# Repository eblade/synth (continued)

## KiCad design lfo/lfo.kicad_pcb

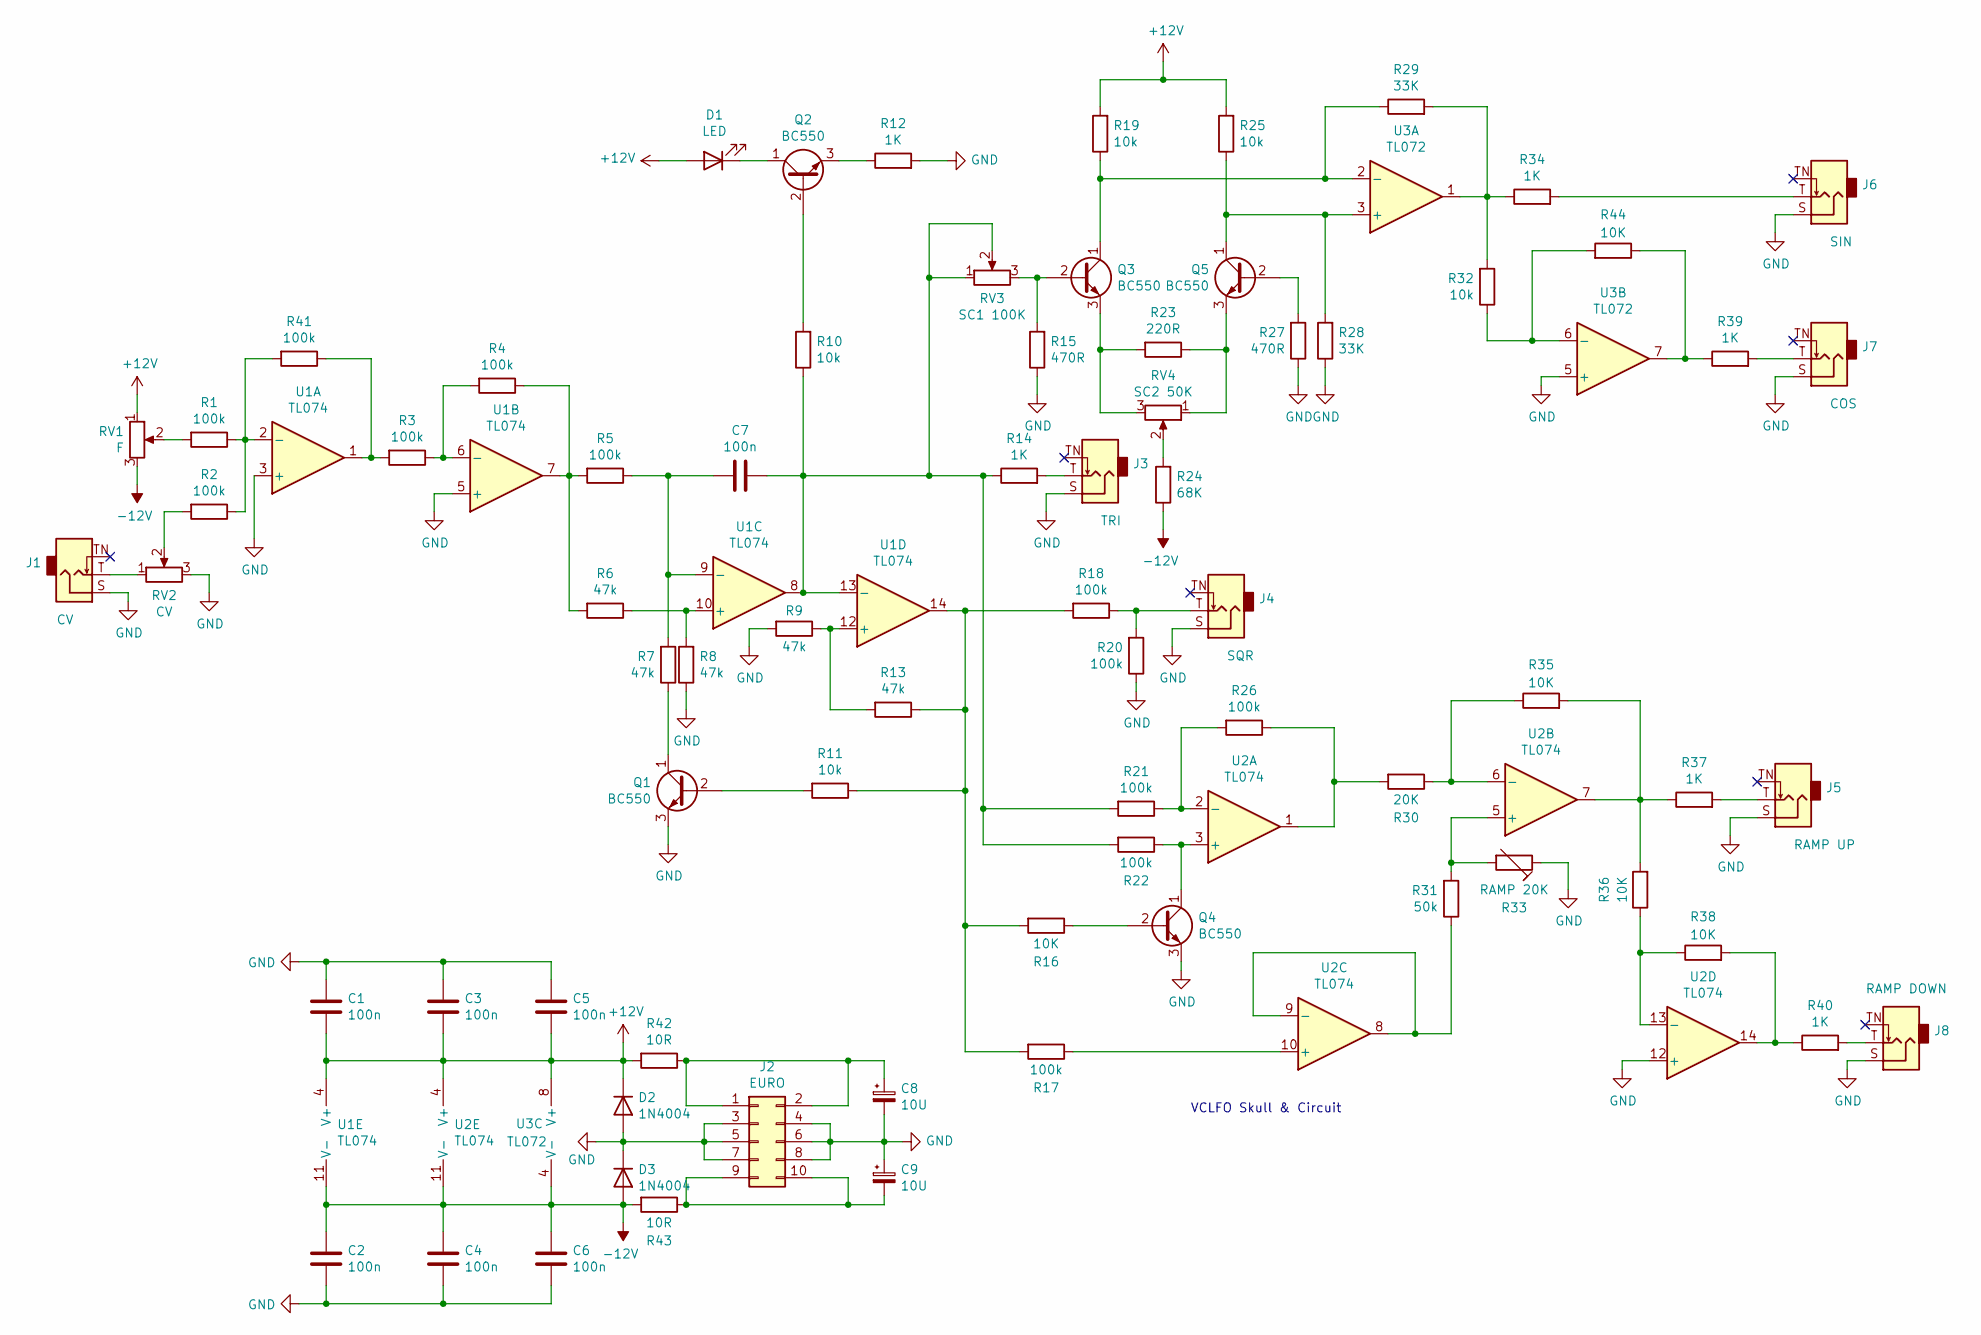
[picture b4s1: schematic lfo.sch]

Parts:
C1, C2, C3, C4, C5, C6, C7: 100n; C_Disc_D5.0mm_W2.5mm_P2.50mm
C8, C9: 10U; CP_Radial_D5.0mm_P2.00mm
D1: LED; LED_D3.0mm
D2, D3: 1N4004; D_5W_P12.70mm_Horizontal
J1: CV; Jack_3.5mm_QingPu_WQP-PJ398SM_Vertical_CircularHoles
J2: EURO; PinHeader_2x05_P2.54mm_Vertical
J3: TRI; Jack_3.5mm_QingPu_WQP-PJ398SM_Vertical_CircularHoles
J4: SQR; Jack_3.5mm_QingPu_WQP-PJ398SM_Vertical_CircularHoles
J5: RAMP UP; Jack_3.5mm_QingPu_WQP-PJ398SM_Vertical_CircularHoles
J6: SIN; Jack_3.5mm_QingPu_WQP-PJ398SM_Vertical_CircularHoles
J7: COS; Jack_3.5mm_QingPu_WQP-PJ398SM_Vertical_CircularHoles
J8: RAMP DOWN; Jack_3.5mm_QingPu_WQP-PJ398SM_Vertical_CircularHoles
Q1, Q2, Q3, Q4, Q5: BC550; TO-92_Inline
R1, R2, R3, R4, R5, R17, R18, R20, R21, R22, R26, R41: 100k; R_Axial_DIN0204_L3.6mm_D1.6mm_P7.62mm_Horizontal
R6, R7, R8, R9, R13: 47k; R_Axial_DIN0204_L3.6mm_D1.6mm_P7.62mm_Horizontal
R10, R11, R19, R25, R32: 10k; R_Axial_DIN0204_L3.6mm_D1.6mm_P7.62mm_Horizontal
R12, R14, R34, R37, R39, R40: 1K; R_Axial_DIN0204_L3.6mm_D1.6mm_P7.62mm_Horizontal
R15, R27: 470R; R_Axial_DIN0204_L3.6mm_D1.6mm_P7.62mm_Horizontal
R16, R35, R36, R38, R44: 10K; R_Axial_DIN0204_L3.6mm_D1.6mm_P7.62mm_Horizontal
R23: 220R; R_Axial_DIN0204_L3.6mm_D1.6mm_P7.62mm_Horizontal
R24: 68K; R_Axial_DIN0204_L3.6mm_D1.6mm_P7.62mm_Horizontal
R28, R29: 33K; R_Axial_DIN0204_L3.6mm_D1.6mm_P7.62mm_Horizontal
R30: 20K; R_Axial_DIN0204_L3.6mm_D1.6mm_P7.62mm_Horizontal
R31: 50k; R_Axial_DIN0204_L3.6mm_D1.6mm_P7.62mm_Horizontal
R33: RAMP 20K; Potentiometer_Bourns_3296W_Vertical
R42, R43: 10R; R_Axial_DIN0204_L3.6mm_D1.6mm_P7.62mm_Horizontal
RV1: F; Potentiometer_Alps_RK09L_Single_Vertical
RV2: CV; Potentiometer_Alps_RK09L_Single_Vertical
RV3: SC1 100K; Potentiometer_Bourns_3296W_Vertical
RV4: SC2 50K; Potentiometer_Bourns_3296W_Vertical
U1, U2: TL074; DIP-14_W7.62mm_Socket_LongPads
U3: TL072; DIP-8_W7.62mm_Socket_LongPads

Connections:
+12V: C1.1, C3.1, C5.1, D1.2 (A), D2.1 (K), R19.2, R25.2, R42.2, RV1.1, U1.4 (V+), U2.4 (V+), U3.8 (V+)
-12V: C2.2, C4.2, C6.2, D3.2 (A), R24.1, R43.2, RV1.3, U1.11 (V-), U2.11 (V-), U3.4 (V-)
GND: C1.2, C2.1, C3.2, C4.1, C5.2, C6.1, C8.2, C9.1, D2.2 (A), D3.1 (K), J1.S, J2.3, J2.4, J2.5, J2.6, J2.7, J2.8, J3.S, J4.S, J5.S, J6.S, J7.S, J8.S, Q1.3 (E), Q4.3 (E), R8.1, R9.2, R12.2, R15.1, R20.1, R27.1, R28.1, R33.1, RV2.3, U1.3 (+), U1.5 (+), U2.12 (+), U3.5 (+)
unnamed: C7.1, R10.1, R14.1, R21.2, R22.2, RV3.1, RV3.2, U1.8, U1.13 (-)
unnamed: C7.2, R5.1, R7.2, U1.9 (-)
unnamed: C8.1, J2.1, J2.2, R42.1
unnamed: C9.2, J2.9, J2.10, R43.1
unnamed: D1.1 (K), Q2.1 (C)
unnamed: J1.T, RV2.1
unnamed: J3.T, R14.2
unnamed: J4.T, R18.1, R20.2
unnamed: J5.T, R37.2
unnamed: J6.T, R34.2
unnamed: J7.T, R39.2
unnamed: J8.T, R40.2
unnamed: Q1.1 (C), R7.1
unnamed: Q1.2 (B), R11.2
unnamed: Q2.2 (B), R10.2
unnamed: Q2.3 (E), R12.1
unnamed: Q3.1 (C), R19.1, R29.1, U3.2 (-)
unnamed: Q3.2 (B), R15.2, RV3.3
unnamed: Q3.3 (E), R23.2, RV4.3
unnamed: Q4.1 (C), R22.1, U2.3 (+)
unnamed: Q4.2 (B), R16.1
unnamed: Q5.1 (C), R25.1, R28.2, U3.3 (+)
unnamed: Q5.2 (B), R27.2
unnamed: Q5.3 (E), R23.1, RV4.1
unnamed: R1.1, R2.1, R41.2, U1.2 (-)
unnamed: R1.2, RV1.2
unnamed: R2.2, RV2.2
unnamed: R3.1, R4.2, U1.6 (-)
unnamed: R3.2, R41.1, U1.1
unnamed: R4.1, R5.2, R6.2, U1.7
unnamed: R6.1, R8.2, U1.10 (+)
unnamed: R11.1, R13.1, R16.2, R17.2, R18.2, U1.14
unnamed: R9.1, R13.2, U1.12 (+)
unnamed: R17.1, U2.10 (+)
unnamed: R21.1, R26.2, U2.2 (-)
unnamed: R24.2, RV4.2
unnamed: R26.1, R30.2, U2.1
unnamed: R29.2, R32.2, R34.1, U3.1
unnamed: R30.1, R35.1, U2.6 (-)
unnamed: R31.1, U2.8, U2.9 (-)
unnamed: R31.2, R33.2, U2.5 (+)
unnamed: R32.1, R44.2, U3.6 (-)
unnamed: R35.2, R36.2, R37.1, U2.7
unnamed: R36.1, R38.1, U2.13 (-)
unnamed: R38.2, R40.1, U2.14
unnamed: R39.1, R44.1, U3.7

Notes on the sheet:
VCLFO Skull & Circuit

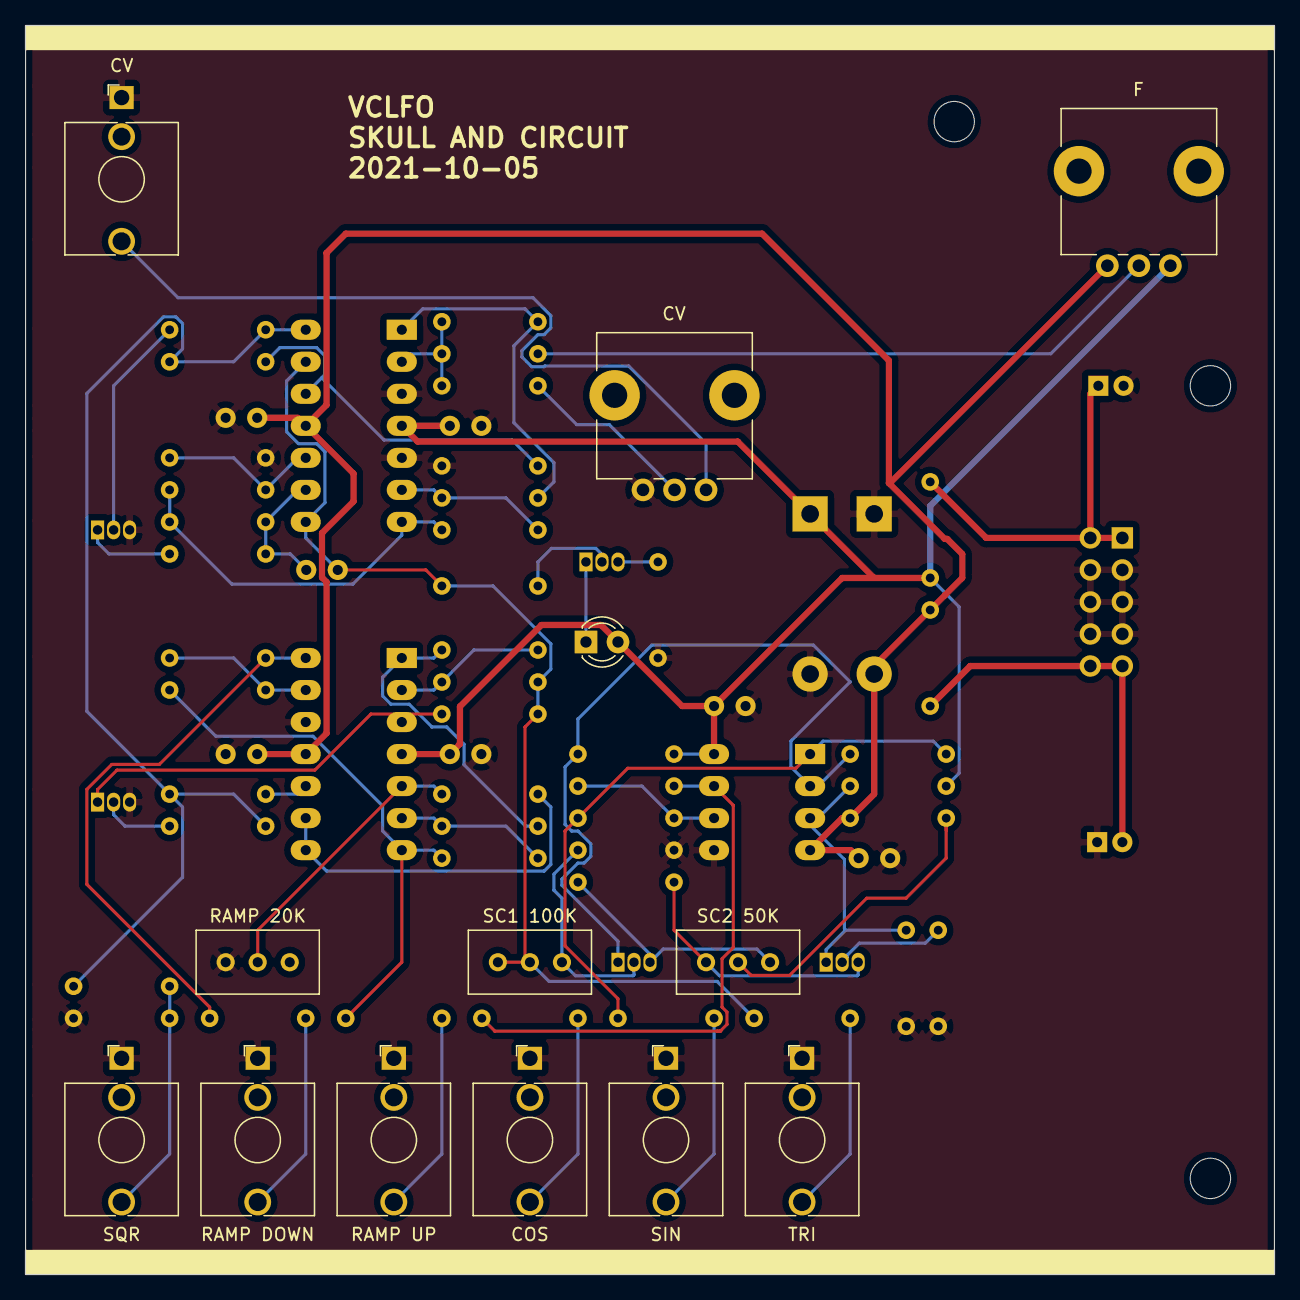
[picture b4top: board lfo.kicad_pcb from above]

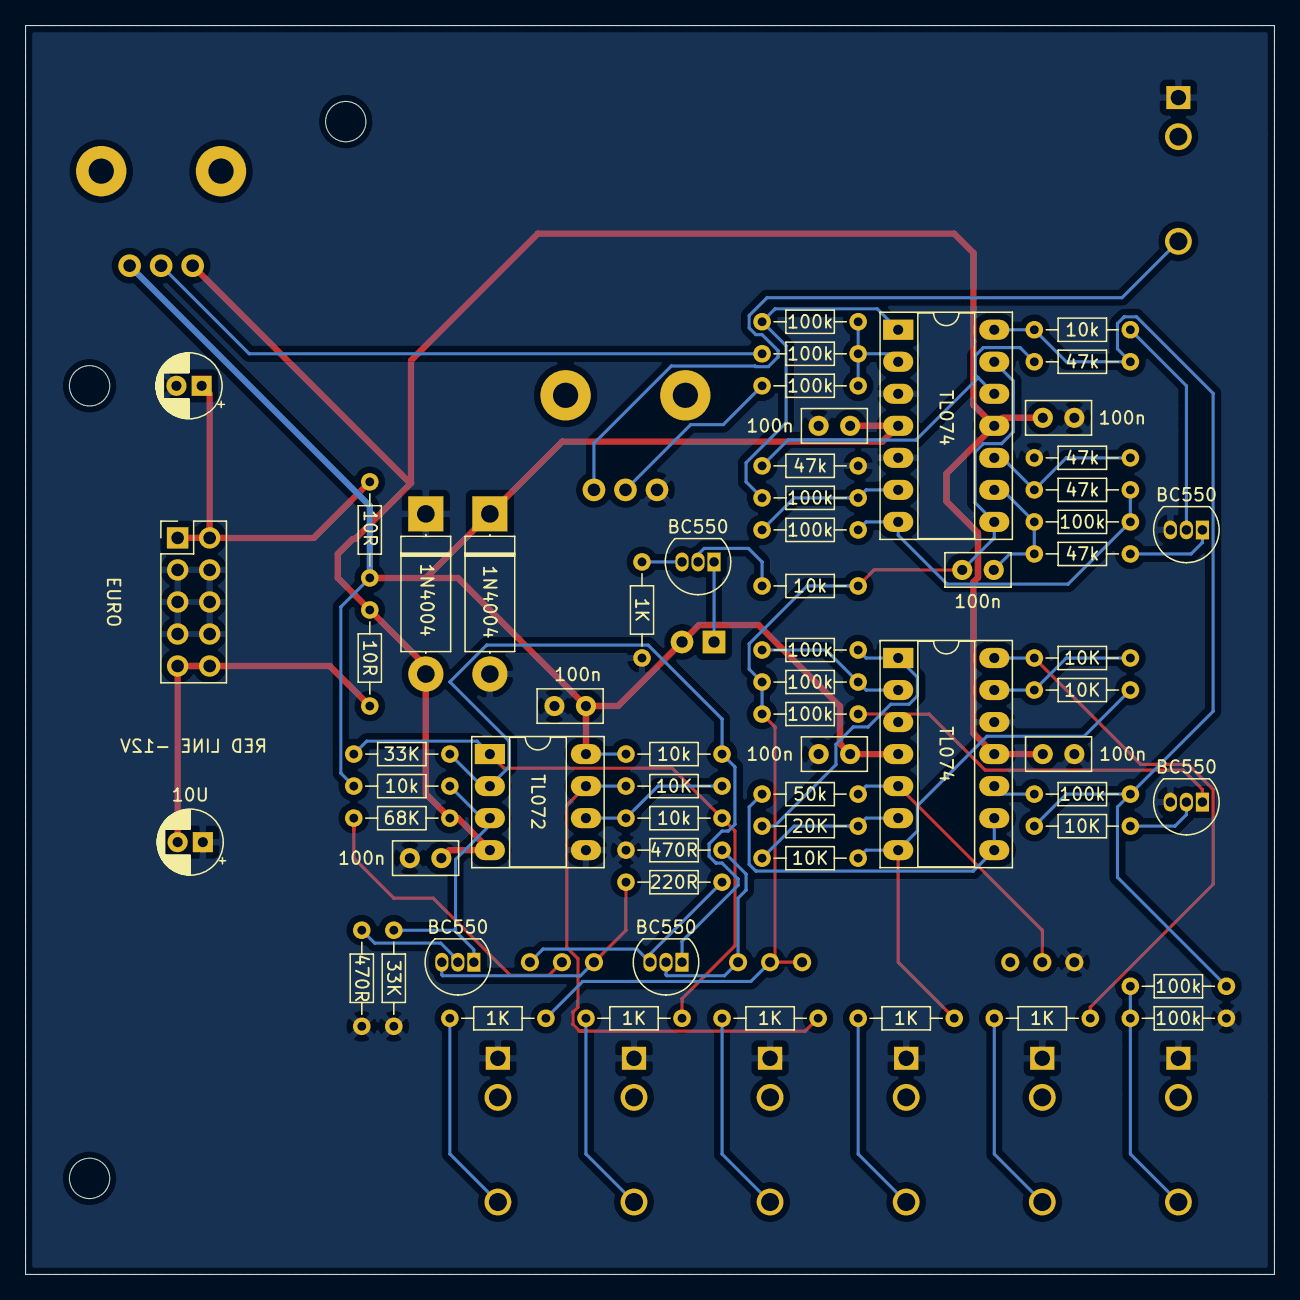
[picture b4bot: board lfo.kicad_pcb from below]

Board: 2 copper layers, 99.1 x 99.1 mm, 76 parts (63 on the bottom side), 49 nets.

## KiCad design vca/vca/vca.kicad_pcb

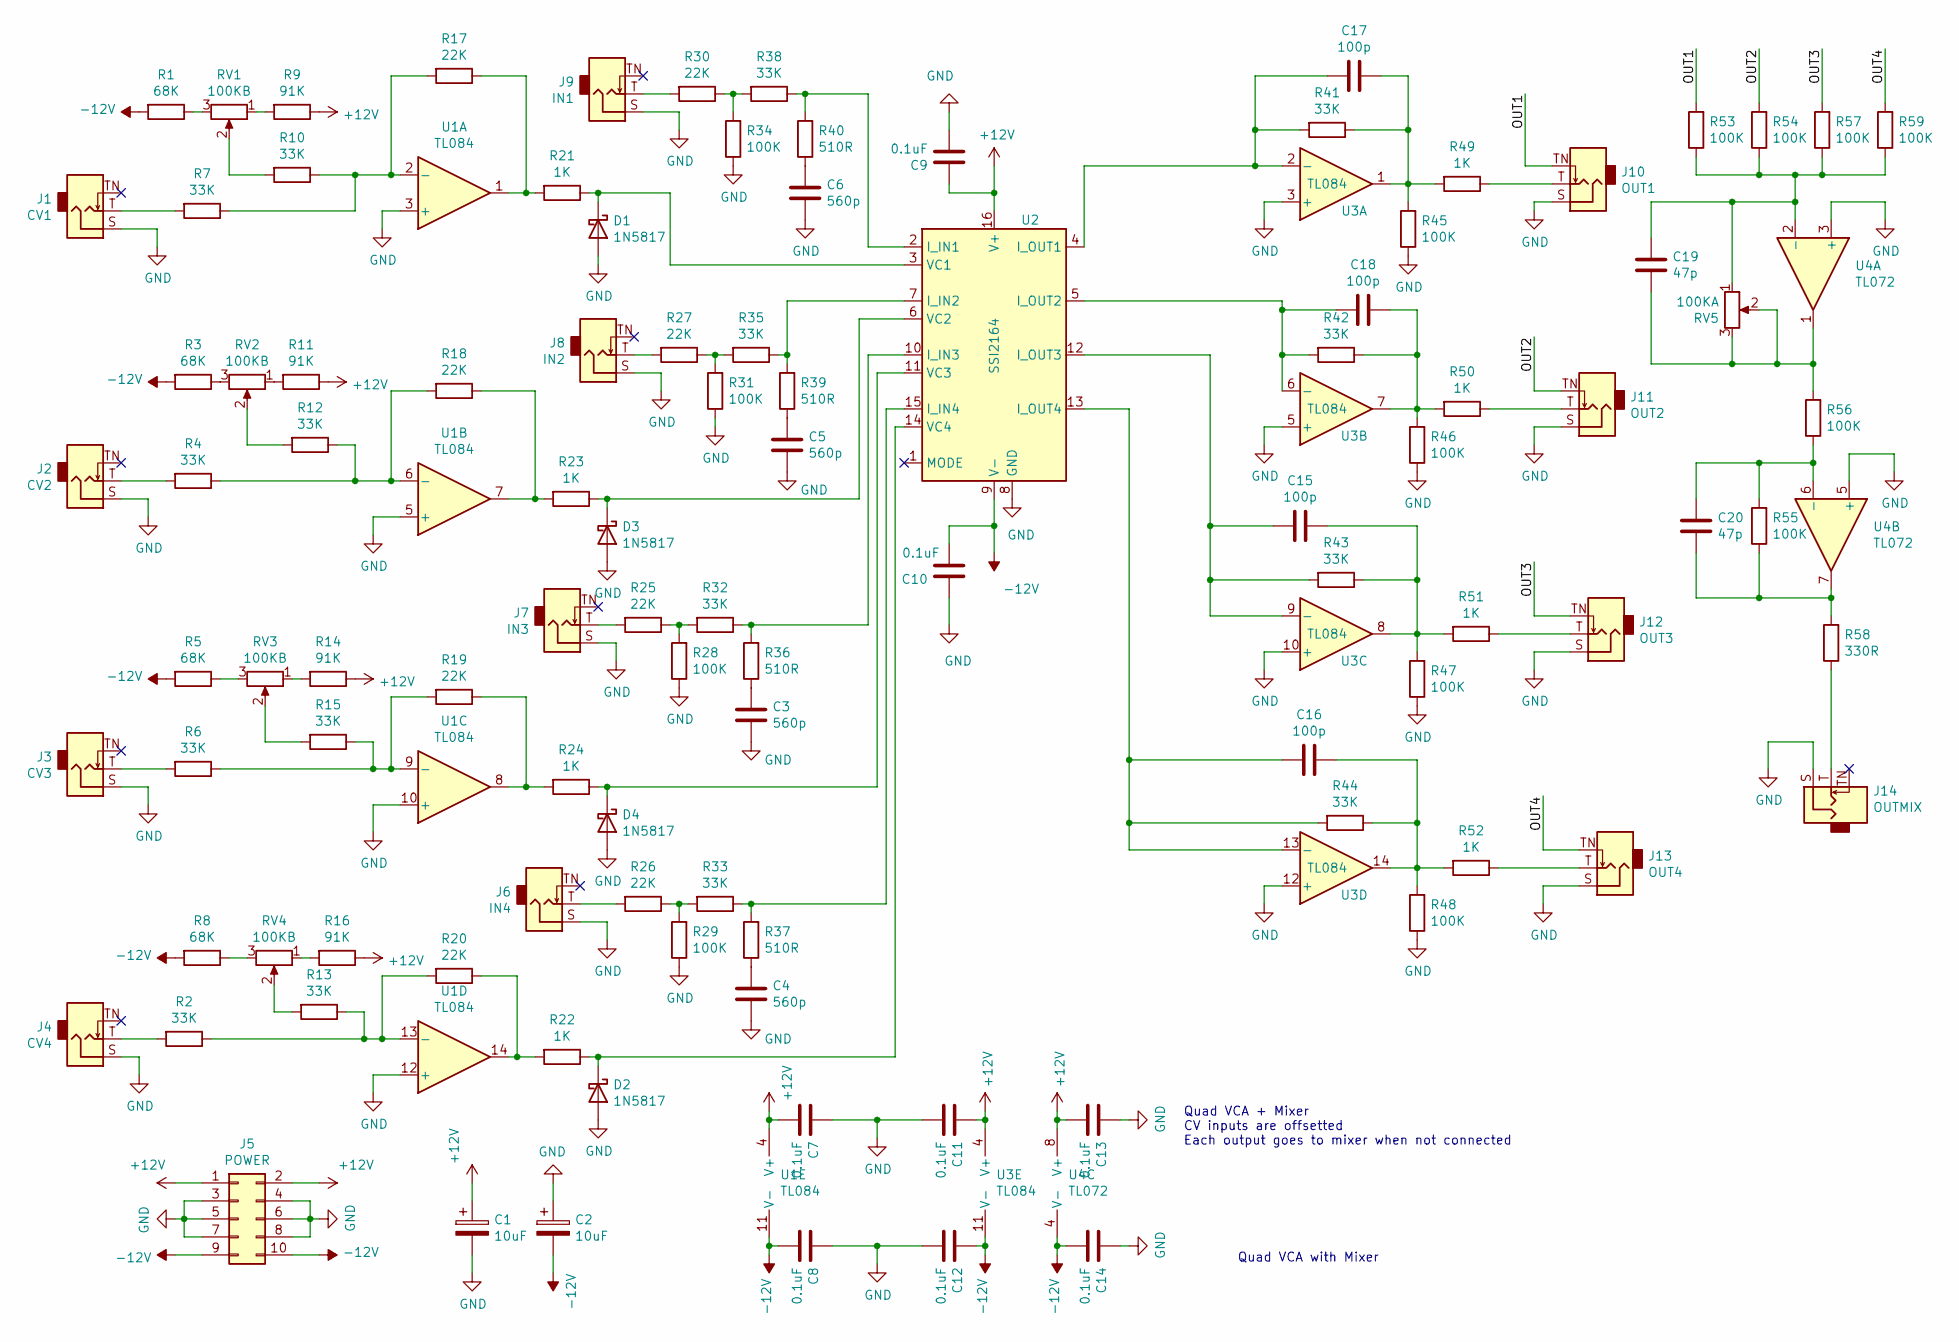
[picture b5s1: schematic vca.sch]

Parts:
C1, C2: 10uF; CP_Radial_D5.0mm_P2.50mm
C3, C4, C5, C6: 560p; C_Disc_D7.5mm_W2.5mm_P5.00mm
C7, C8, C9, C10, C11, C12, C13, C14: 0.1uF; C_Disc_D7.5mm_W2.5mm_P5.00mm
C15, C16, C17, C18: 100p; C_Disc_D7.5mm_W2.5mm_P5.00mm
C19, C20: 47p; C_Disc_D7.5mm_W2.5mm_P5.00mm
D1, D2, D3, D4: 1N5817; D_DO-41_SOD81_P10.16mm_Horizontal
J1: CV1; Jack_3.5mm_QingPu_WQP-PJ398SM_Vertical_CircularHoles
J2: CV2; Jack_3.5mm_QingPu_WQP-PJ398SM_Vertical_CircularHoles
J3: CV3; Jack_3.5mm_QingPu_WQP-PJ398SM_Vertical_CircularHoles
J4: CV4; Jack_3.5mm_QingPu_WQP-PJ398SM_Vertical_CircularHoles
J5: POWER; PinHeader_2x05_P2.54mm_Vertical
J6: IN4; Jack_3.5mm_QingPu_WQP-PJ398SM_Vertical_CircularHoles
J7: IN3; Jack_3.5mm_QingPu_WQP-PJ398SM_Vertical_CircularHoles
J8: IN2; Jack_3.5mm_QingPu_WQP-PJ398SM_Vertical_CircularHoles
J9: IN1; Jack_3.5mm_QingPu_WQP-PJ398SM_Vertical_CircularHoles
J10: OUT1; Jack_3.5mm_QingPu_WQP-PJ398SM_Vertical_CircularHoles
J11: OUT2; Jack_3.5mm_QingPu_WQP-PJ398SM_Vertical_CircularHoles
J12: OUT3; Jack_3.5mm_QingPu_WQP-PJ398SM_Vertical_CircularHoles
J13: OUT4; Jack_3.5mm_QingPu_WQP-PJ398SM_Vertical_CircularHoles
J14: OUTMIX; Jack_3.5mm_QingPu_WQP-PJ398SM_Vertical_CircularHoles
R1, R3, R5, R8: 68K; R_Axial_DIN0204_L3.6mm_D1.6mm_P7.62mm_Horizontal
R2, R4, R6, R7, R10, R12, R13, R15, R32, R33, R35, R38, R41, R42, R43, R44: 33K; R_Axial_DIN0204_L3.6mm_D1.6mm_P7.62mm_Horizontal
R9, R11, R14, R16: 91K; R_Axial_DIN0204_L3.6mm_D1.6mm_P7.62mm_Horizontal
R17, R18, R19, R20, R25, R26, R27, R30: 22K; R_Axial_DIN0204_L3.6mm_D1.6mm_P7.62mm_Horizontal
R21, R22, R23, R24, R49, R50, R51, R52: 1K; R_Axial_DIN0204_L3.6mm_D1.6mm_P7.62mm_Horizontal
R28, R29, R31, R34, R45, R46, R47, R48, R53, R54, R55, R56, R57, R59: 100K; R_Axial_DIN0204_L3.6mm_D1.6mm_P7.62mm_Horizontal
R36, R37, R39, R40: 510R; R_Axial_DIN0204_L3.6mm_D1.6mm_P7.62mm_Horizontal
R58: 330R; R_Axial_DIN0204_L3.6mm_D1.6mm_P7.62mm_Horizontal
RV1, RV2, RV3, RV4: 100KB; Potentiometer_Alps_RK09L_Single_Vertical
RV5: 100KA; Potentiometer_Alps_RK09L_Single_Vertical
U1, U3: TL084; DIP-14_W7.62mm_Socket
U2: SSI2164; DIP-16_W7.62mm_Socket
U4: TL072; DIP-8_W7.62mm_Socket

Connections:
+12V: C1.1, C7.2, C9.1, C11.1, C13.2, J5.1, J5.2, R9.1, R11.1, R14.1, R16.1, U1.4 (V+), U2.16 (V+), U3.4 (V+), U4.8 (V+)
-12V: C2.2, C8.2, C10.2, C12.1, C14.2, J5.9, J5.10, R1.2, R3.2, R5.2, R8.2, U1.11 (V-), U2.9 (V-), U3.11 (V-), U4.4 (V-)
/OUT1: J10.TN, R53.2
/OUT2: J11.TN, R54.2
/OUT3: J12.TN, R57.2
/OUT4: J13.TN, R59.2
GND: C1.2, C2.1, C3.2, C4.2, C5.2, C6.2, C7.1, C8.1, C9.2, C10.1, C11.2, C12.2, C13.1, C14.1, D1.2 (A), D2.2 (A), D3.2 (A), D4.2 (A), J1.S, J2.S, J3.S, J4.S, J5.3, J5.4, J5.5, J5.6, J5.7, J5.8, J6.S, J7.S, J8.S, J9.S, J10.S, J11.S, J12.S, J13.S, J14.S, R28.1, R29.1, R31.1, R34.1, R45.1, R46.1, R47.1, R48.1, U1.3 (+), U1.5 (+), U1.10 (+), U1.12 (+), U2.8 (GND), U3.3 (+), U3.5 (+), U3.10 (+), U3.12 (+), U4.3 (+), U4.5 (+); also elsewhere on the board
unnamed: C3.1, R36.1
unnamed: C4.1, R37.1
unnamed: C5.1, R39.1
unnamed: C6.1, R40.1
unnamed 11: C15.1, R43.1, R47.2, R51.2, U3.8; also elsewhere on the board
unnamed 12: C15.2, R43.2, U2.12 (I_OUT3), U3.9 (-); also elsewhere on the board
unnamed: C16.1, R44.1, R48.2, R52.2, U3.14
unnamed: C16.2, R44.2, U2.13 (I_OUT4), U3.13 (-)
unnamed: C17.1, R41.1, R45.2, R49.2, U3.1
unnamed: C17.2, R41.2, U2.4 (I_OUT1), U3.2 (-)
unnamed: C18.1, R42.1, R46.2, R50.2, U3.7
unnamed: C18.2, R42.2, U2.5 (I_OUT2), U3.6 (-)
unnamed: C19.1, R56.2, RV5.2, RV5.3, U4.1
unnamed: C19.2, R53.1, R54.1, R57.1, R59.1, RV5.1, U4.2 (-)
unnamed: C20.1, R55.1, R58.2, U4.7
unnamed: C20.2, R55.2, R56.1, U4.6 (-)
unnamed: D1.1 (K), R21.1, U2.3 (VC1)
unnamed: D2.1 (K), R22.1, U2.14 (VC4)
unnamed: D3.1 (K), R23.1, U2.6 (VC2)
unnamed: D4.1 (K), R24.1, U2.11 (VC3)
unnamed: J1.T, R7.2
unnamed: J2.T, R4.2
unnamed: J3.T, R6.2
unnamed: J4.T, R2.2
unnamed: J6.T, R26.2
unnamed: J7.T, R25.2
unnamed: J8.T, R27.2
unnamed: J9.T, R30.2
unnamed: J10.T, R49.1
unnamed: J11.T, R50.1
unnamed: J12.T, R51.1
unnamed: J13.T, R52.1
unnamed: J14.T, R58.1
unnamed: R1.1, RV1.3
unnamed: R3.1, RV2.3
unnamed: R5.1, RV3.3
unnamed: R8.1, RV4.3
unnamed: R9.2, RV1.1
unnamed: R7.1, R10.1, R17.2, U1.2 (-)
unnamed: R10.2, RV1.2
unnamed: R11.2, RV2.1
unnamed: R4.1, R12.1, R18.2, U1.6 (-)
unnamed: R12.2, RV2.2
unnamed: R2.1, R13.1, R20.2, U1.13 (-)
unnamed: R13.2, RV4.2
unnamed: R14.2, RV3.1
unnamed: R6.1, R15.1, R19.2, U1.9 (-)
unnamed: R15.2, RV3.2
unnamed: R16.2, RV4.1
unnamed: R17.1, R21.2, U1.1
unnamed: R18.1, R23.2, U1.7
unnamed: R19.1, R24.2, U1.8
unnamed: R20.1, R22.2, U1.14
unnamed: R25.1, R28.2, R32.2
unnamed: R26.1, R29.2, R33.2
unnamed: R27.1, R31.2, R35.2
unnamed 72: R30.1, R34.2, R38.2; also elsewhere on the board
unnamed: R32.1, R36.2, U2.10 (I_IN3)
unnamed: R33.1, R37.2, U2.15 (I_IN4)
unnamed: R35.1, R39.2, U2.7 (I_IN2)
unnamed: R38.1, R40.2, U2.2 (I_IN1)

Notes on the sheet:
Quad VCA + Mixer CV inputs are offsetted Each output goes to mixer when not connected
Quad VCA with Mixer

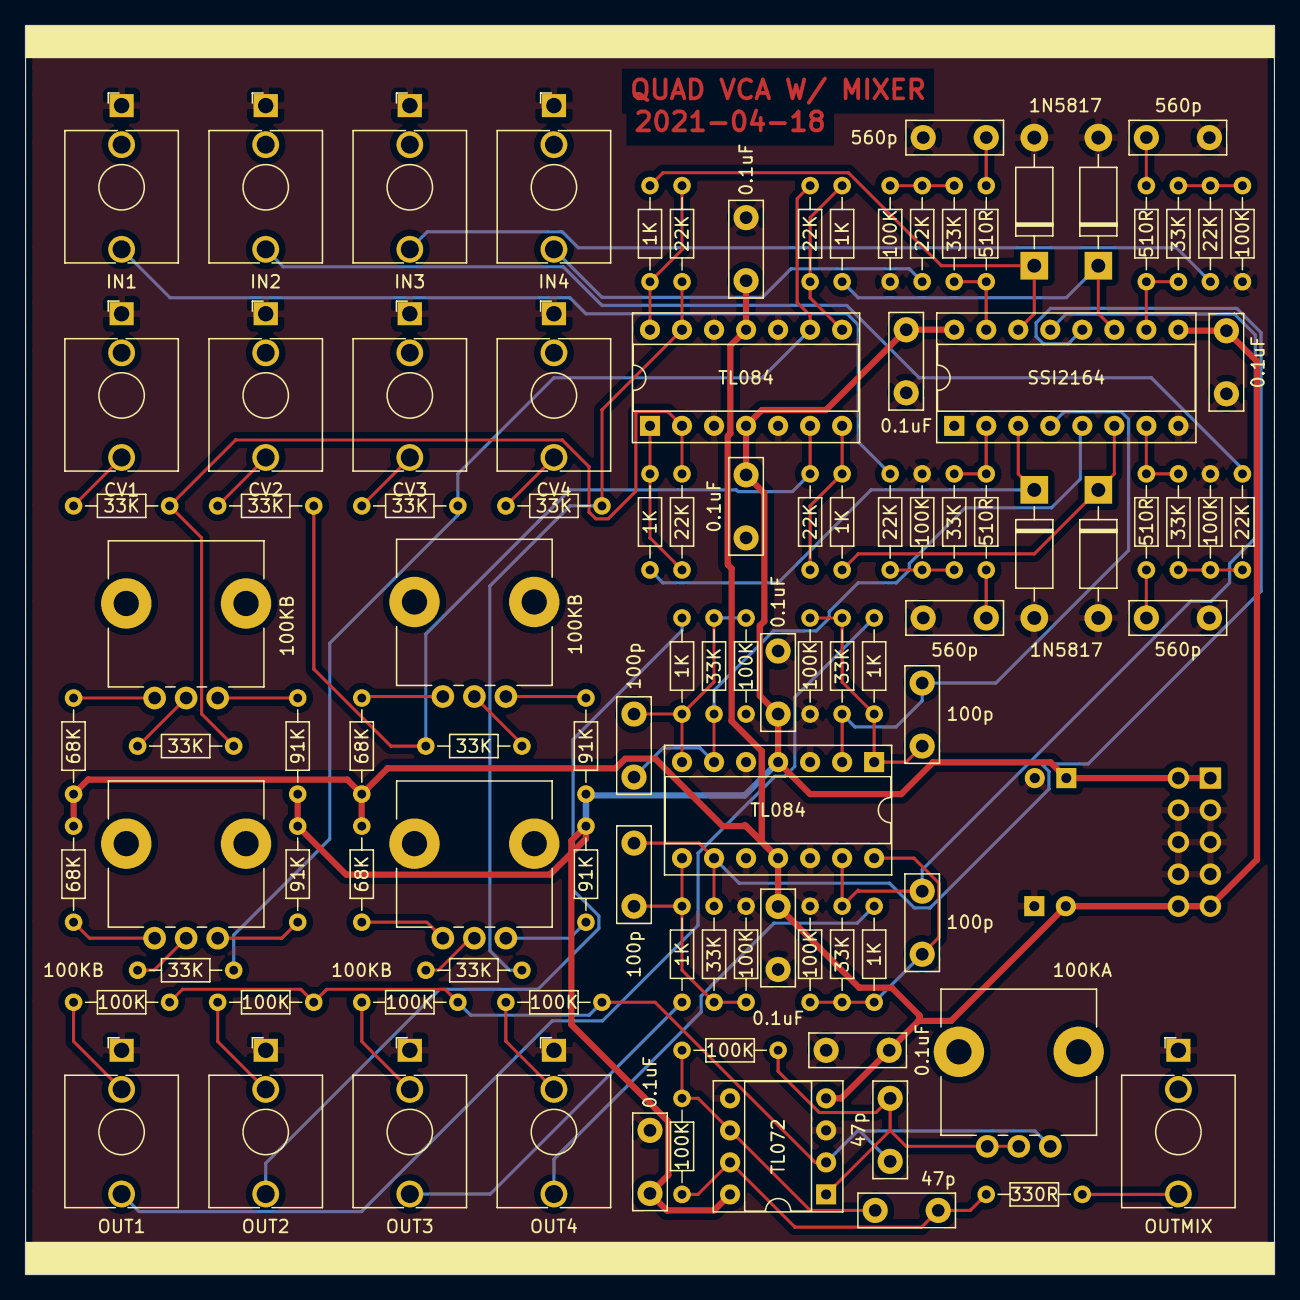
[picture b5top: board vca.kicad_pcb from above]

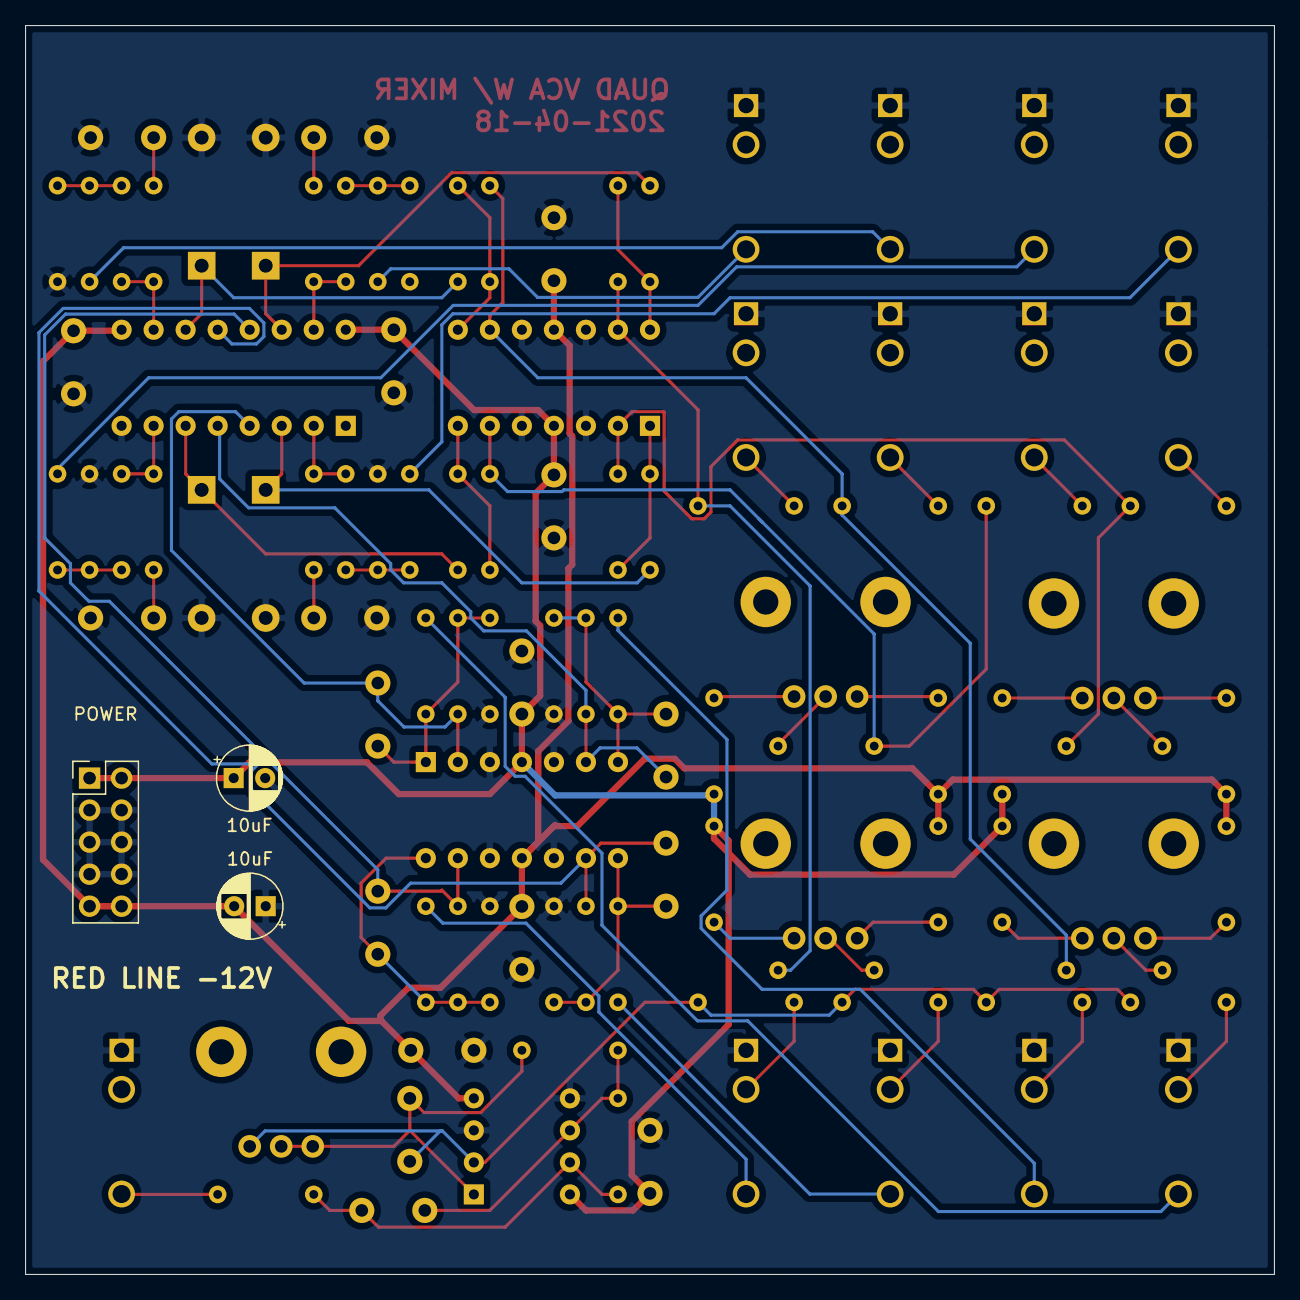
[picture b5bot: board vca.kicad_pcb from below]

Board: 2 copper layers, 99.1 x 99.1 mm, 106 parts (3 on the bottom side), 68 nets.

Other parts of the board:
Cr: 100p; C_Disc_D7.5mm_W2.5mm_P5.00mm
Rw: 100K; R_Axial_DIN0204_L3.6mm_D1.6mm_P7.62mm_Horizontal

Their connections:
GND: Rw.1; also elsewhere on the board
unnamed 11: Cr.1; also elsewhere on the board
unnamed 12: Cr.2; also elsewhere on the board
unnamed 72: Rw.2; also elsewhere on the board

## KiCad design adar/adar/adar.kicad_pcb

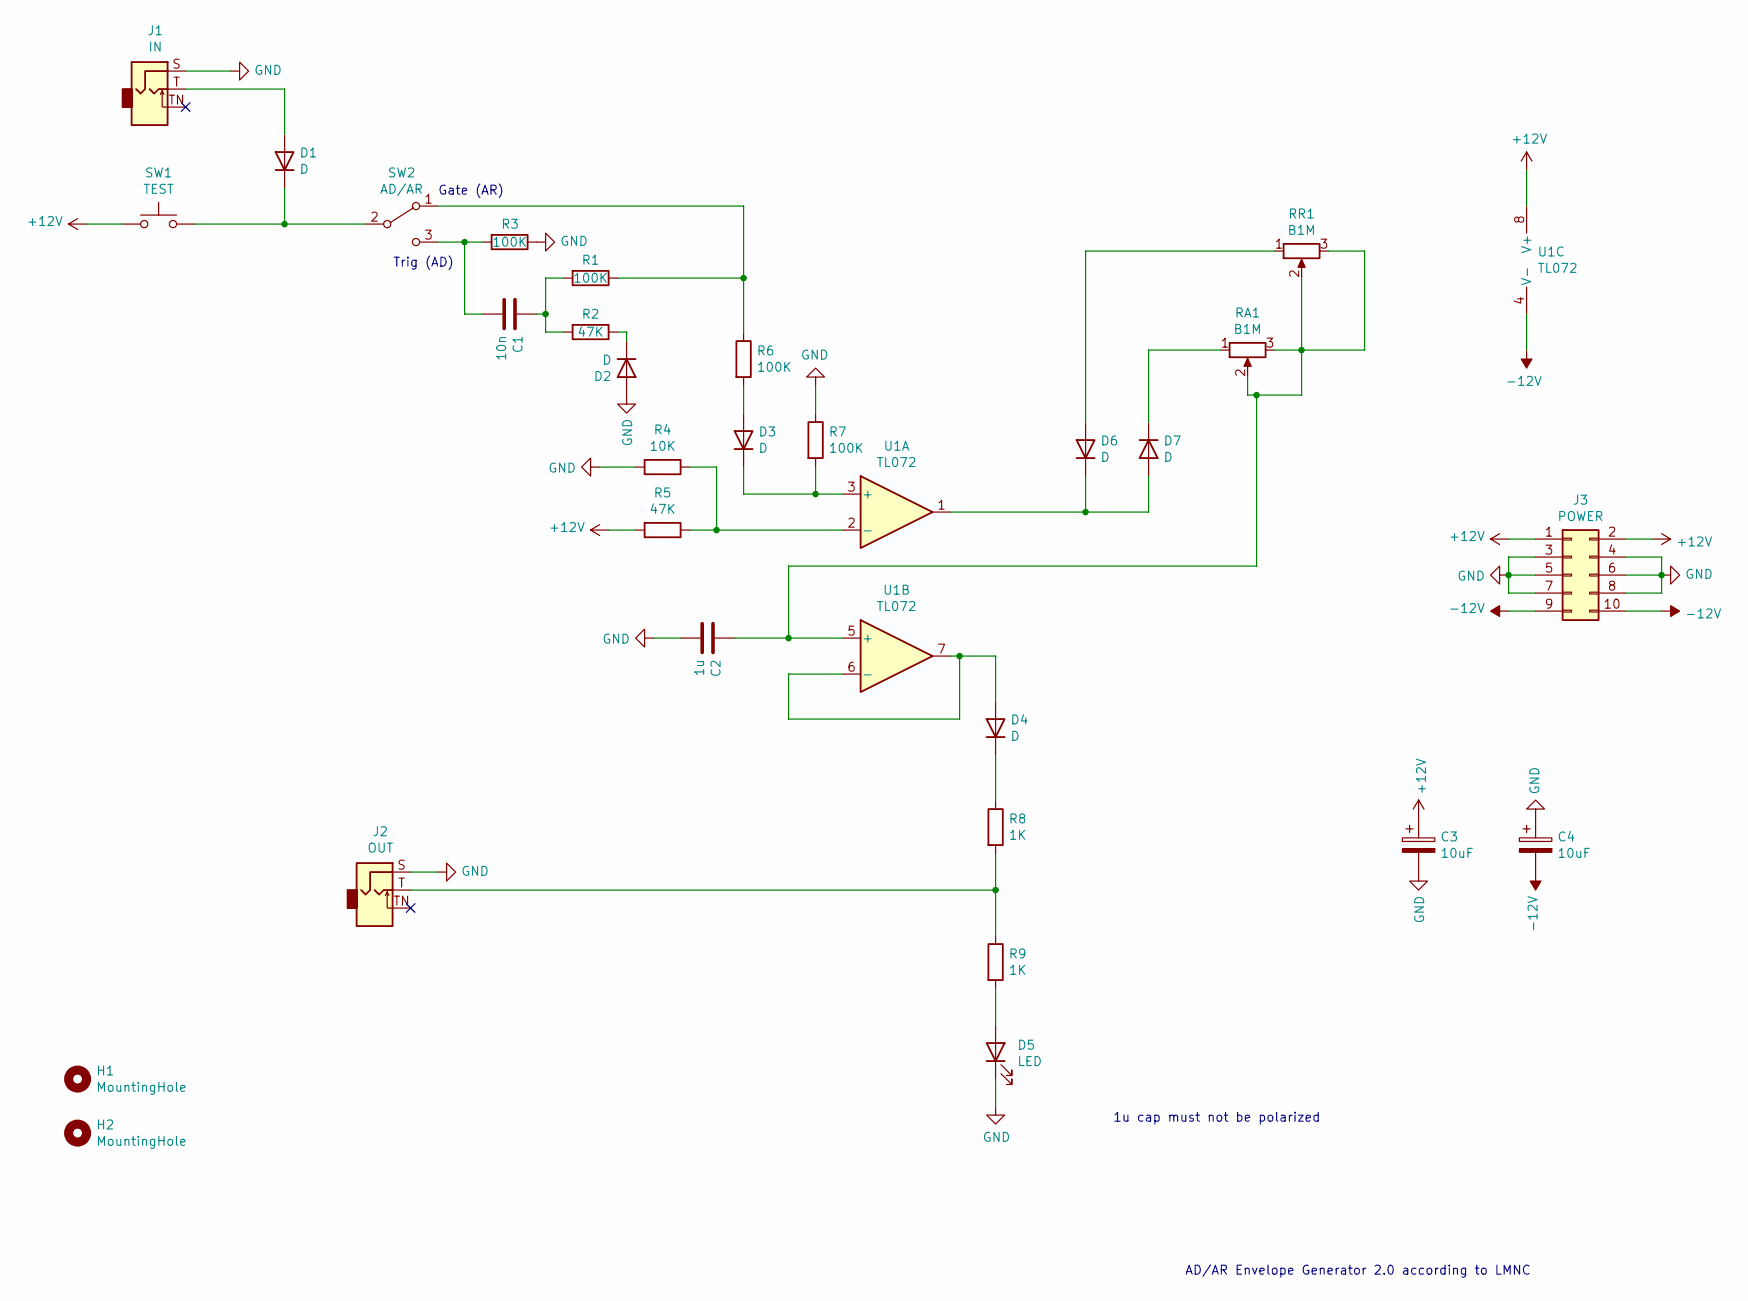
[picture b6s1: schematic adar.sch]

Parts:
C1: 10n; C_Disc_D7.5mm_W2.5mm_P5.00mm
C2: 1u; C_Disc_D7.5mm_W2.5mm_P5.00mm
C3, C4: 10uF; CP_Radial_D5.0mm_P2.50mm
D1, D2, D3, D4, D6, D7: D; D_DO-34_SOD68_P7.62mm_Horizontal
D5: LED; LED_D3.0mm
H1, H2: MountingHole; MountingHole_3.2mm_M3_Pad
J1: IN; Jack_3.5mm_QingPu_WQP-PJ398SM_Vertical_CircularHoles
J2: OUT; Jack_3.5mm_QingPu_WQP-PJ398SM_Vertical_CircularHoles
J3: POWER; PinHeader_2x05_P2.54mm_Vertical
R1, R3, R6, R7: 100K; R_Axial_DIN0204_L3.6mm_D1.6mm_P7.62mm_Horizontal
R2, R5: 47K; R_Axial_DIN0204_L3.6mm_D1.6mm_P7.62mm_Horizontal
R4: 10K; R_Axial_DIN0204_L3.6mm_D1.6mm_P7.62mm_Horizontal
R8, R9: 1K; R_Axial_DIN0204_L3.6mm_D1.6mm_P7.62mm_Horizontal
RA1: B1M; PinHeader_1x03_P2.54mm_Vertical
RR1: B1M; PinHeader_1x03_P2.54mm_Vertical
SW1: TEST; SW_PUSH_6mm
SW2: AD/AR; PinHeader_1x03_P2.54mm_Vertical
U1: TL072; DIP-8_W7.62mm_Socket

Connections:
+12V: C3.1, J3.1, J3.2, R5.2, SW1.1, U1.8 (V+)
-12V: C4.2, J3.9, J3.10, U1.4 (V-)
GND: C2.2, C3.2, C4.1, D2.2 (A), D5.1 (K), J1.S, J2.S, J3.3, J3.4, J3.5, J3.6, J3.7, J3.8, R3.1, R4.2, R7.1
unnamed: C1.1, R1.2, R2.2
unnamed: C1.2, R3.2, SW2.3 (C)
unnamed: C2.1, RA1.2, RA1.3, RR1.2, RR1.3, U1.5 (+)
unnamed: D1.1 (K), SW1.2, SW2.2 (B)
unnamed: D1.2 (A), J1.T
unnamed: D2.1 (K), R2.1
unnamed: D3.1 (K), R7.2, U1.3 (+)
unnamed: D3.2 (A), R6.2
unnamed: D4.1 (K), R8.1
unnamed: D4.2 (A), U1.6 (-), U1.7
unnamed: D5.2 (A), R9.2
unnamed: D6.1 (K), D7.2 (A), U1.1
unnamed: D6.2 (A), RR1.1
unnamed: D7.1 (K), RA1.1
unnamed: J2.T, R8.2, R9.1
unnamed: R1.1, R6.1, SW2.1 (A)
unnamed: R4.1, R5.1, U1.2 (-)

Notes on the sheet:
AD/AR Envelope Generator 2.0 according to LMNC
1u cap must not be polarized
Gate (AR)
Trig (AD)
